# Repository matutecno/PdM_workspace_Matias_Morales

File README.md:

STM32 University Projects - Coursework Solutions
This repository contains solutions for the exercises proposed in my Embedded Systems courses.

⚠️ Important: Library Dependency
These projects rely on shared drivers stored in the Personal_libs folder. If a project does not compile, you must link this folder to your environment:

Right-click on the project -> Select "Properties".

Go to C/C++ General -> Paths and Symbols.

Select the "Source Location" tab.

Click on "Link Folder...".

Folder name: Enter Personal_libs.

Check the box "Link to folder in the file system".

Click "Browse..." and select your local Personal_libs directory.

Click OK -> Apply and Close.

📂 How to Add New Libraries to the Project
If you add a new module (like Delay or JSNSR04T) to the Personal_libs folder, follow these steps to ensure the IDE and the Compiler (GCC) recognize them:

1. Refresh the Project Explorer
After moving or creating files in your Linux file system (ThinkPad), the IDE needs to sync:

Right-click on the Personal_libs folder in the Project Explorer.

Select Refresh (or simply press F5). The new Inc and Src folders should now be visible.

2. Configure Include Paths (CRITICAL)
Even if the files are visible in the explorer, the compiler won't find the .h files unless you explicitly tell it where to look:

Right-click on the project name -> Properties.

Navigate to C/C++ Build -> Settings.

Under the Tool Settings tab, go to: MCU GCC Compiler -> Include paths.

Click the Add... icon (the page with the + symbol).

Click on Workspace..., navigate to the specific Inc folder (e.g., Personal_libs/Delay/Inc), and click OK.

Click Apply and Close.

Note: You must repeat step 2 for every new library module you create to avoid "No such file or directory" errors during compilation.

Project Directory

📂 Excercise 1
LED Blink: Basic implementation using External Interrupts (EXTI) to handle push-button inputs, avoiding CPU blocking.

📂 Excercise 2
Non-blocking Delays: Timing implementation using the HAL_GetTick() method to allow multitasking.

Bonus Exercise: Found in the folder ending in _3.

Custom Driver: I developed a modular library (del.c and del.h) to encapsulate delay logic for future projects.

Theory: Check Notes.txt within the project folder for the technical Q&A.

📂 Exercise 3
No comments

📂 Exercise 4
Finite machine states

📂 Exercise 5

Part 1: Polling UART Driver

**Platform:** Nucleo-F446RE (STM32F446RE, 84 MHz)
**IDE:** STM32CubeIDE
**Course:** Microcontroller Programming — FIUBA

## Description

Implementation of a UART driver over USART2 in polling mode, without DMA or interrupts. The driver encapsulates the HAL handle and exposes a high-level API for sending and receiving strings.

## Serial Port Configuration

| Parameter       | Value     |
|-----------------|-----------|
| Instance        | USART2    |
| Baud rate       | 9600      |
| Data bits       | 8         |
| Parity          | Odd       |
| Stop bits       | 1         |
| Flow control    | None      |
| Oversampling    | x16       |
| Pins            | PA2 (TX), PA3 (RX) |

> The serial terminal must be configured as **9600 8-Odd-1**.

## Driver Files

| File | Description |
|------|-------------|
| `STM32CubeIDE/Drivers/API_uart.c/Src/API_uart.c` | Driver implementation |
| `STM32CubeIDE/Drivers/API_uart.c/Inc/API_uart.h` | Public interface |

## API

```c
bool uartInit(void);
void uartSendString(uint8_t *pstring);
void uartSendStringSize(uint8_t *pstring, uint16_t size);
void uartReceiveStringSize(uint8_t *pstring, uint16_t size);
```

- `uartInit`: initializes USART2 and prints the port configuration to the console. Returns `1` on success, `0` on error.
- `uartSendString`: transmits a null-terminated string.
- `uartSendStringSize`: transmits exactly `size` bytes, one byte at a time.
- `uartReceiveStringSize`: receives bytes until `\n` or until `size` bytes are read. Blocks until reception is complete.

## Main Behavior

On startup, `uartInit` prints the port configuration. The main loop then:
1. Sends `buffer` over UART
2. Waits 500 ms
3. Sends `buffer2` over UART
4. Waits 500 ms
5. Sends `buffer3` over UART and waits to receive a string from the terminal
6. The received string is stored in `buffer3` for the next cycle

## Clock

- Source: HSE 8 MHz
- PLL: PLLM=8, PLLN=336, PLLP=DIV4 → SYSCLK = 84 MHz
- APB1 = 42 MHz (USART2 clock source)
- Voltage scaling: SCALE2

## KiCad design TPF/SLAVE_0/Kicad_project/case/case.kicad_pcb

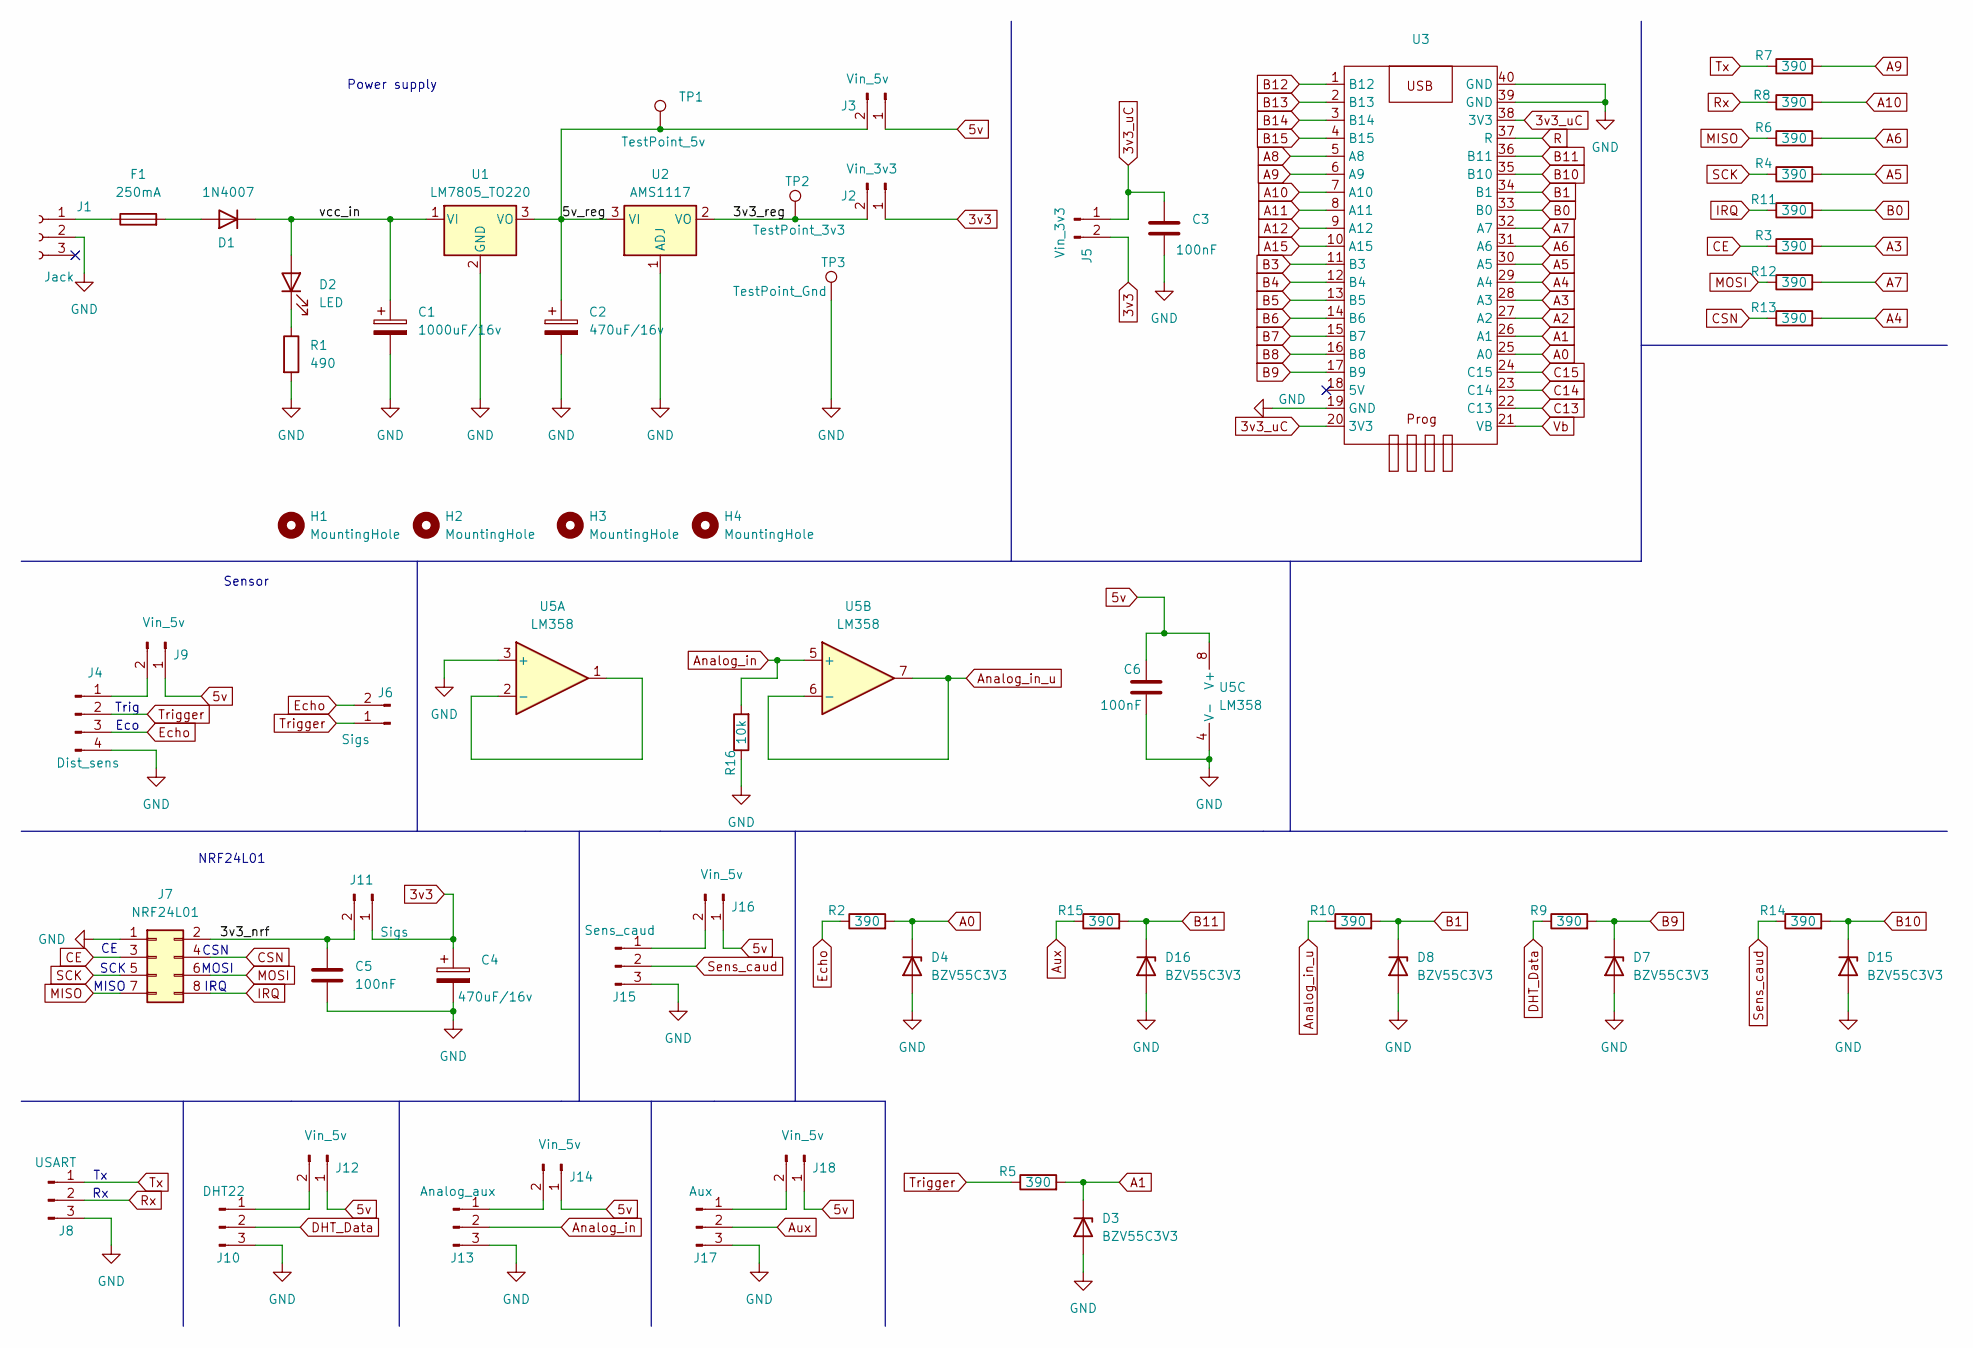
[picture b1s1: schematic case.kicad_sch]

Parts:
C1: 1000uF/16v; CP_Radial_D10.0mm_P5.00mm
C2, C4: 470uF/16v; CP_Radial_D8.0mm_P3.50mm
C3, C5, C6: 100nF; C_1206_3216Metric
D1: 1N4007; D_SMA_Handsoldering
D2: LED; LED_D3.0mm
D3, D4, D7, D8, D15, D16: BZV55C3V3; D_MiniMELF
F1: 250mA; Fuse_Littelfuse_395Series
H1, H2, H3, H4: MountingHole; MountingHole_3mm
J1: Jack; BarrelJack_Horizontal
J2, J5: Vin_3v3; PinHeader_1x02_P2.54mm_Vertical
J3, J9, J12, J14, J16, J18: Vin_5v; PinHeader_1x02_P2.54mm_Vertical
J4: Dist_sens; JST_PH_B4B-PH-K_1x04_P2.00mm_Vertical
J6, J11: Sigs; PinHeader_1x02_P2.54mm_Vertical
J7: NRF24L01
J8: USART; JST_XA_B03B-XASK-1_1x03_P2.50mm_Vertical
J10: DHT22; JST_XA_B03B-XASK-1_1x03_P2.50mm_Vertical
J13: Analog_aux; JST_XA_B03B-XASK-1_1x03_P2.50mm_Vertical
J15: Sens_caud; JST_XA_B03B-XASK-1_1x03_P2.50mm_Vertical
J17: Aux; JST_XA_B03B-XASK-1_1x03_P2.50mm_Vertical
R1: 490; R_1206_3216Metric
R2, R3, R4, R5, R6, R7, R8, R9, R10, R11, R12, R13, R14, R15: 390; R_1206_3216Metric
R16: 10k; R_1206_3216Metric
TP1: TestPoint_5v; TestPoint_Pad_D2.0mm
TP2: TestPoint_3v3; TestPoint_Pad_D2.0mm
TP3: TestPoint_Gnd; TestPoint_Pad_D2.0mm
U1: LM7805_TO220; TO-220-3_Vertical
U2: AMS1117; SOT-223-3_TabPin2
U3: Bluepill
U5: LM358; SOIC-8_3.9x4.9mm_P1.27mm

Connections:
3v3: C4.1, J2.1, J5.2, J11.1
3v3_uC: C3.1, J5.1, U3.20 (3V3), U3.38 (3V3)
5v: C6.1, J3.1, J9.1, J12.1, J14.1, J16.1, J18.1, U5.8 (V+)
/3v3_nrf: C5.1, J7.2, J11.2
/3v3_reg: J2.2, TP2.1, U2.2 (VO)
/5v_reg: C2.1, J3.2, TP1.1, U1.3 (VO), U2.3 (VI)
/vcc_in: C1.1, D1.1 (K), D2.2 (A), U1.1 (VI)
A0: D4.1 (K), R2.2, U3.25 (A0)
A1: D3.1 (K), R5.2, U3.26 (A1)
A2: U3.27 (A2)
A3: R3.2, U3.28 (A3)
A4: R13.2, U3.29 (A4)
A5: R4.2, U3.30 (A5)
A6: R6.2, U3.31 (A6)
A7: R12.2, U3.32 (A7)
A8: U3.5 (A8)
A9: R7.2, U3.6 (A9)
A10: R8.2, U3.7 (A10)
A11: U3.8 (A11)
A12: U3.9 (A12)
A15: U3.10 (A15)
Analog_in: J13.2, R16.2, U5.5 (+)
Analog_in_u: R10.1, U5.6 (-), U5.7
Aux: J17.2, R15.1
B0: R11.2, U3.33 (B0)
B1: D8.1 (K), R10.2, U3.34 (B1)
B3: U3.11 (B3)
B4: U3.12 (B4)
B5: U3.13 (B5)
B6: U3.14 (B6)
B7: U3.15 (B7)
B8: U3.16 (B8)
B9: D7.1 (K), R9.2, U3.17 (B9)
B10: D15.1 (K), R14.2, U3.35 (B10)
B11: D16.1 (K), R15.2, U3.36 (B11)
B12: U3.1 (B12)
B13: U3.2 (B13)
B14: U3.3 (B14)
B15: U3.4 (B15)
C13: U3.22 (C13)
C14: U3.23 (C14)
C15: U3.24 (C15)
CE: J7.3, R3.1
CSN: J7.4, R13.1
DHT_Data: J10.2, R9.1
Echo: J4.3, J6.2, R2.1
GND: C1.2, C2.2, C3.2, C4.2, C5.2, C6.2, D3.2 (A), D4.2 (A), D7.2 (A), D8.2 (A), D15.2 (A), D16.2 (A), J1.2, J4.4, J7.1, J8.3, J10.3, J13.3, J15.3, J17.3, R1.2, R16.1, TP3.1, U1.2 (GND), U2.1 (ADJ), U3.19 (GND), U3.39 (GND), U3.40 (GND), U5.3 (+), U5.4 (V-)
IRQ: J7.8, R11.1
MISO: J7.7, R6.1
MOSI: J7.6, R12.1
unnamed: D1.2 (A), F1.2
unnamed: D2.1 (K), R1.1
unnamed: F1.1, J1.1
unnamed: J4.1, J9.2
unnamed: J10.1, J12.2
unnamed: J13.1, J14.2
unnamed: J15.1, J16.2
unnamed: J17.1, J18.2
unnamed: U5.1, U5.2 (-)
R: U3.37 (R)
Rx: J8.2, R8.1
SCK: J7.5, R4.1
Sens_caud: J15.2, R14.1
Trigger: J4.2, J6.1, R5.1
Tx: J8.1, R7.1
Vb: U3.21 (VB)

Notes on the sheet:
IRQ
Trig
MOSI
Sensor
MISO
CSN
SCK
Power supply
Eco
NRF24L01

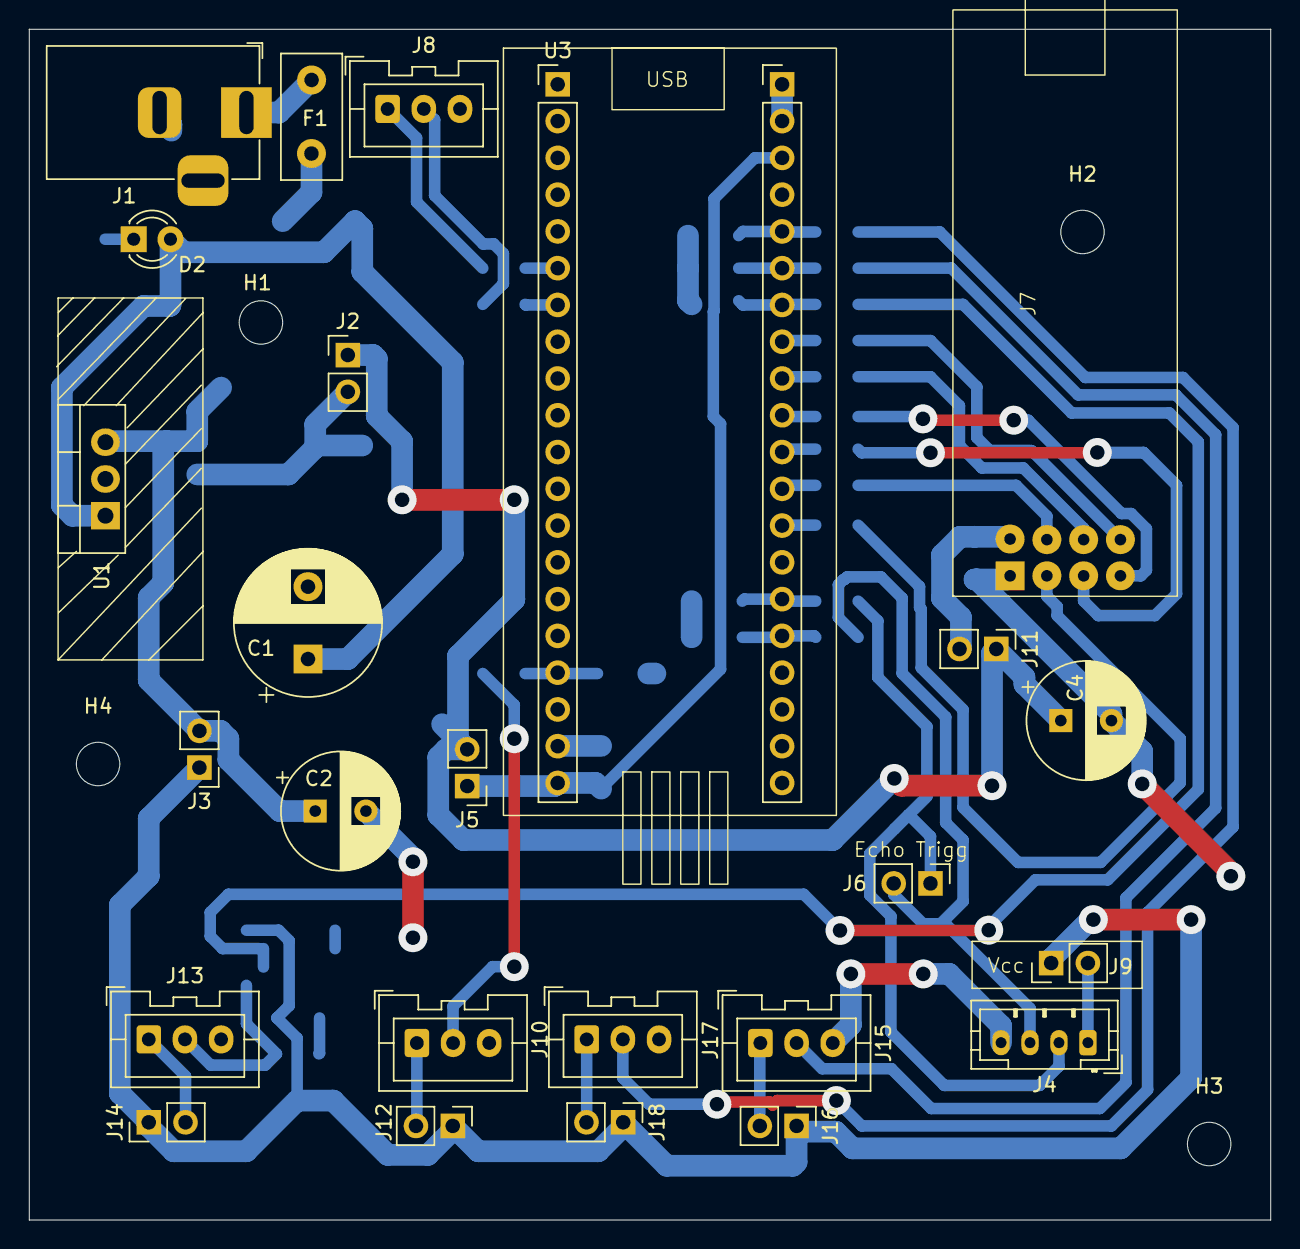
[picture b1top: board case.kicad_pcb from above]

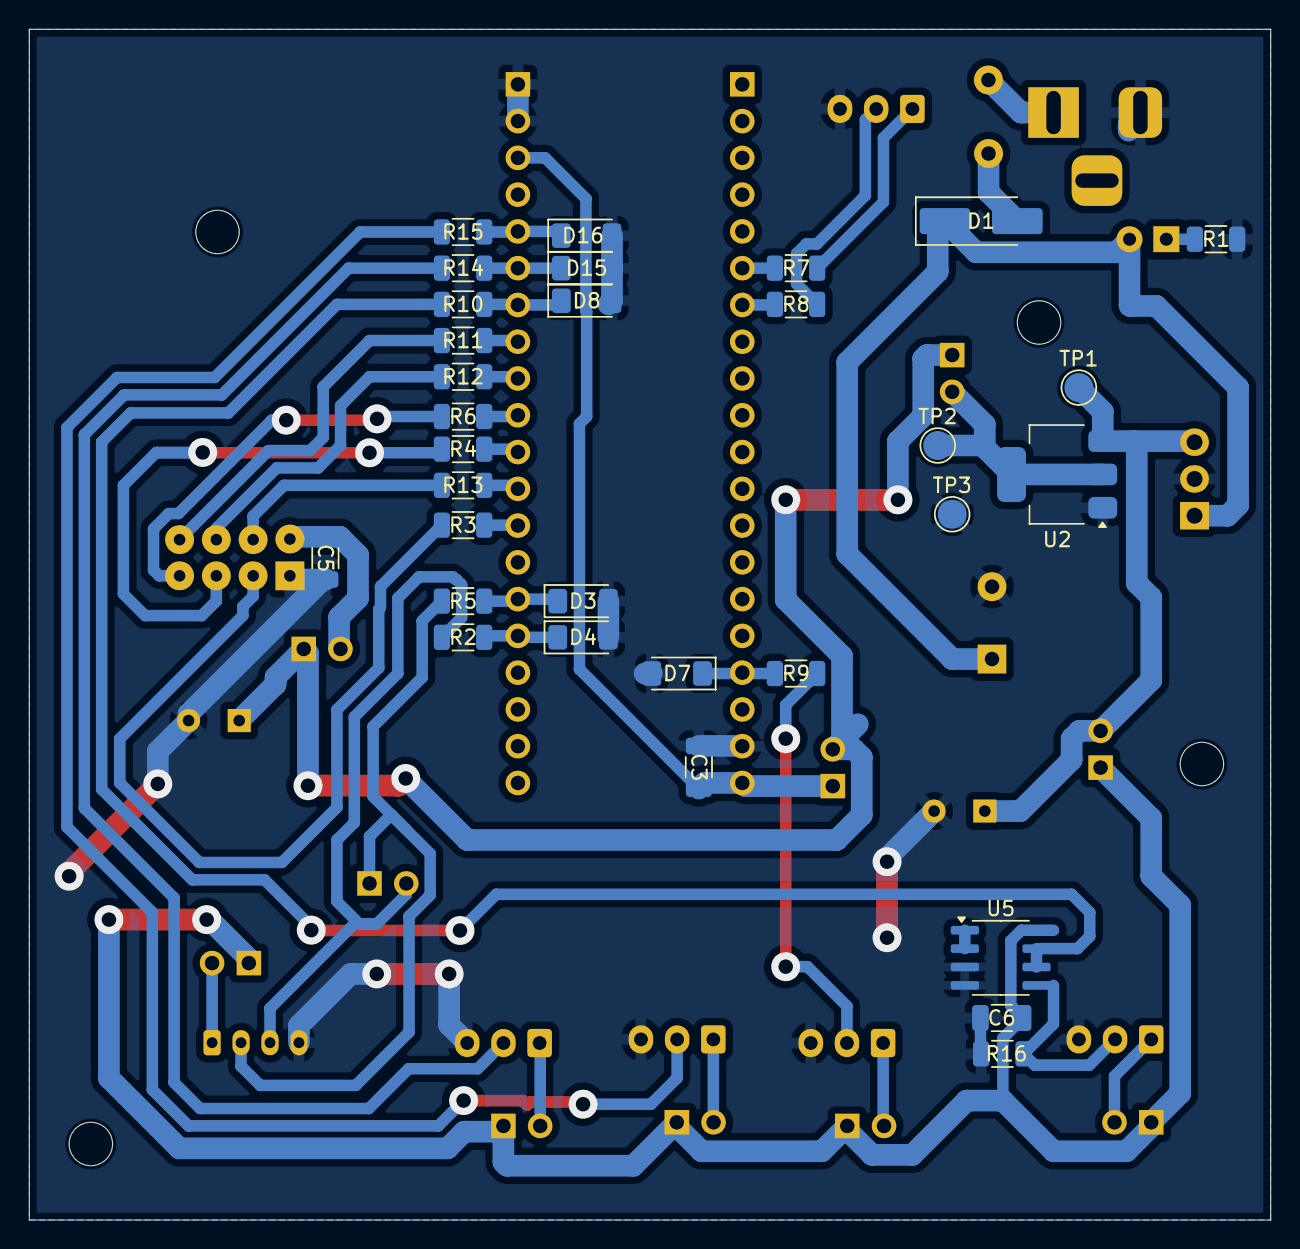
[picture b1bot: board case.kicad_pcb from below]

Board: 2 copper layers, 85.8 x 82.2 mm, 60 parts (31 on the bottom side), 46 nets.

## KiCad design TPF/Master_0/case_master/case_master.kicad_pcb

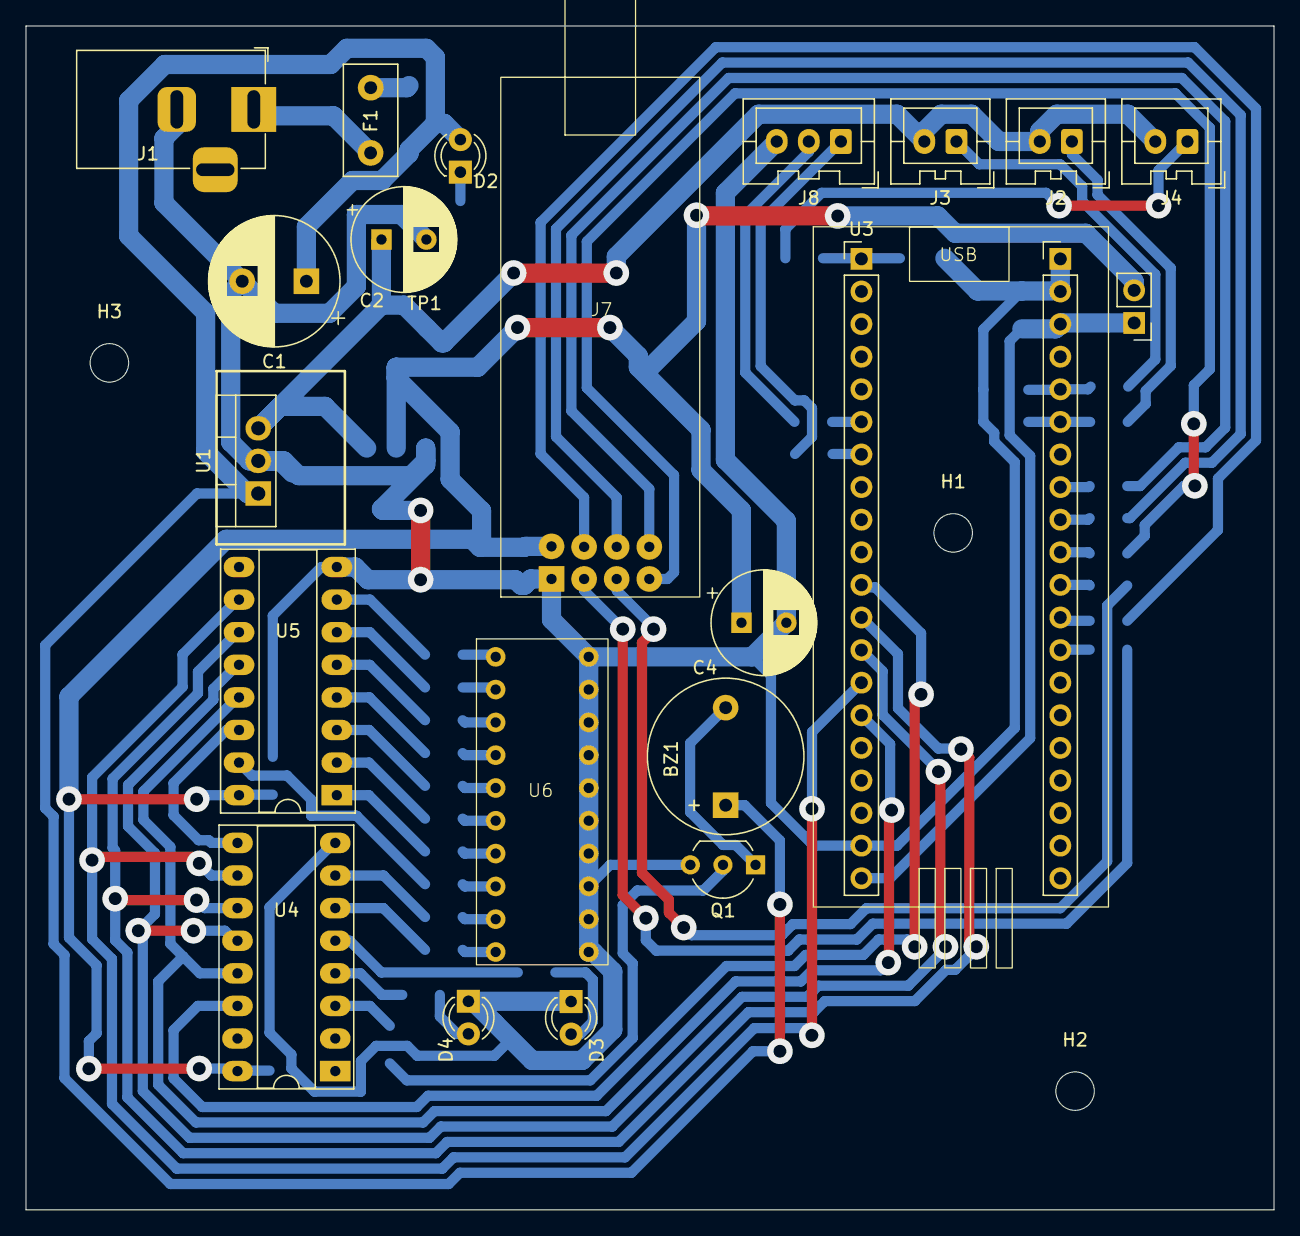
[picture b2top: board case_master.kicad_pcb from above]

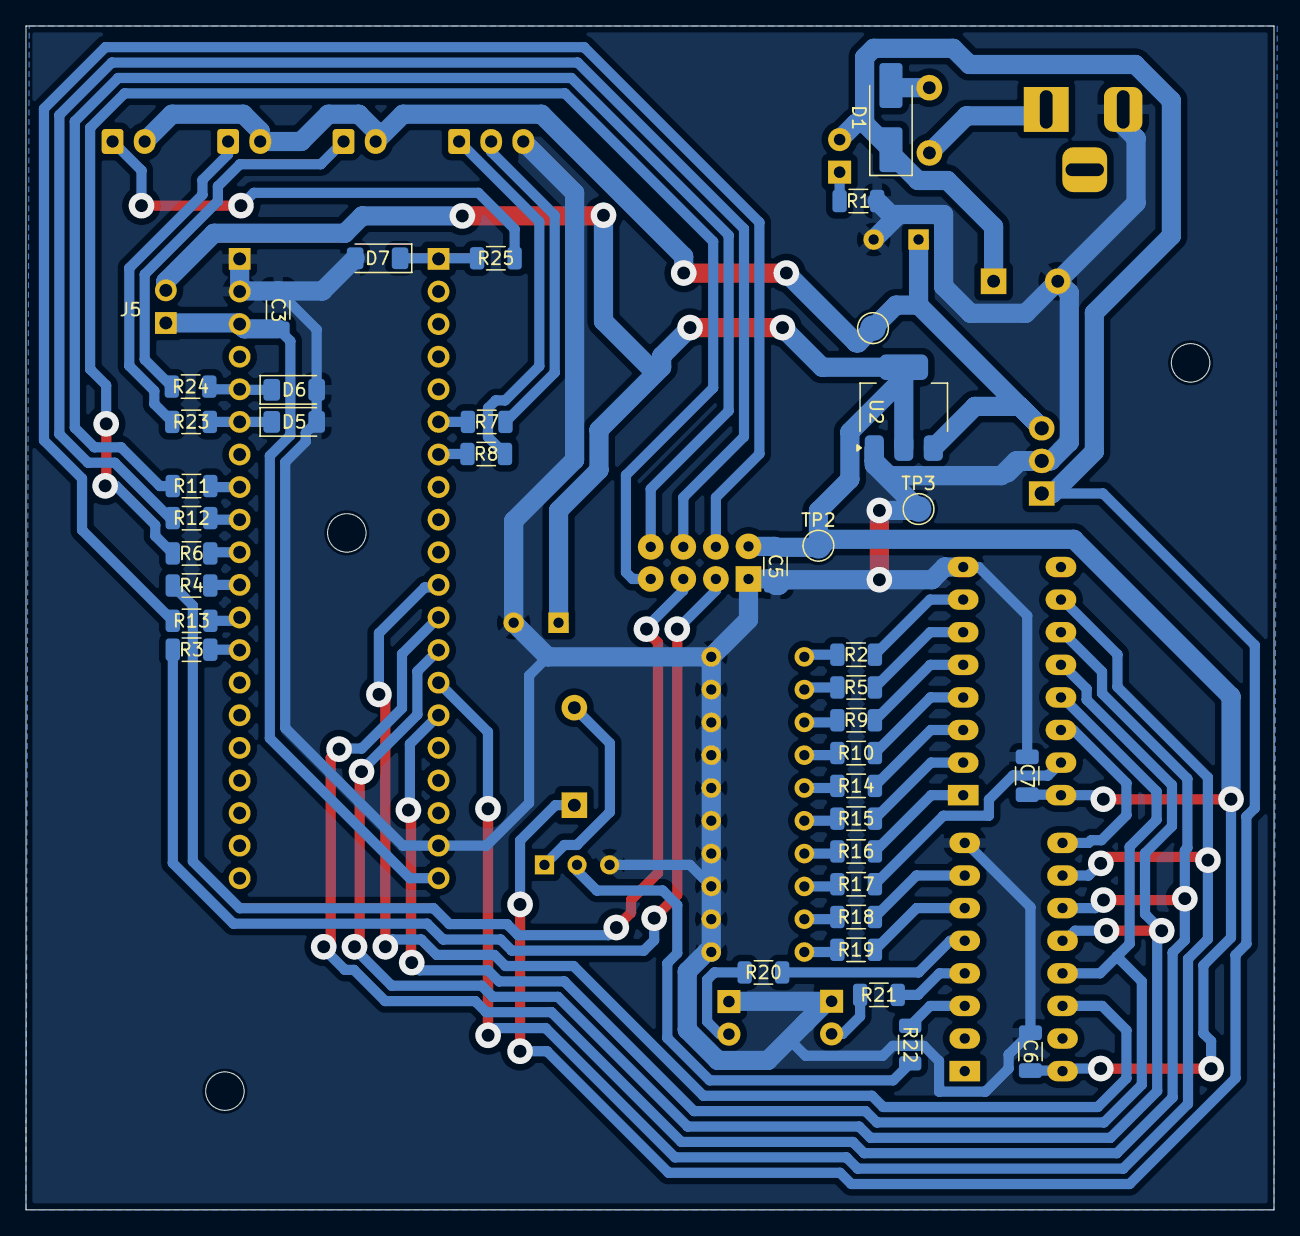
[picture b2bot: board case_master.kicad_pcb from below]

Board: 2 copper layers, 97.2 x 92.2 mm, 61 parts (37 on the bottom side), 63 nets.

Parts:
BZ1: Buzzer; Buzzer_12x9.5RM7.6
C1: 1000uF/16v; CP_Radial_D10.0mm_P5.00mm
C2, C4: 470uF/16v; CP_Radial_D8.0mm_P3.50mm
C3, C5, C6, C7: 100nF; C_1206_3216Metric
D1: 1N4007; D_SMA_Handsoldering
D2, D3, D4: LED; LED_D3.0mm
D5, D6, D7: BZV55C3V3; D_MiniMELF
F1: 250mA; Fuse_Littelfuse_395Series
H1, H2, H3: MountingHole; MountingHole_3mm
J1: Jack; BarrelJack_Horizontal
J2, J3, J4: Pul_0; JST_XA_B02B-XASK-1_1x02_P2.50mm_Vertical
J5: Vin_3v3; PinHeader_1x02_P2.54mm_Vertical
J7: NRF24L01
J8: USART; JST_XA_B03B-XASK-1_1x03_P2.50mm_Vertical
Q1: BC337; TO-92_Inline_Wide
R1: 490; R_1206_3216Metric
R2, R5, R9, R10, R14, R15, R16, R17, R18, R19, R20, R21: 270; R_1206_3216Metric
R3, R4, R6, R7, R8, R11, R12, R13: 390; R_1206_3216Metric
R22: 4k7; R_1206_3216Metric
R23, R24, R25: 1k; R_1206_3216Metric
TP1: TestPoint_5v; TestPoint_Pad_D2.0mm
TP2: TestPoint_3v3; TestPoint_Pad_D2.0mm
TP3: TestPoint_Gnd; TestPoint_Pad_D2.0mm
U1: LM7805_TO220; TO-220-3_Vertical
U2: AMS1117; SOT-223-3_TabPin2
U3: Bluepill
U4, U5: 74HC595; DIP-16_W7.62mm_Socket_LongPads
U6: Dis_1; Led_Bar

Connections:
3v3: C4.1, C5.1, C6.1, C7.1, J5.2, J7.2, TP2.1, U2.2 (VO), U4.16 (VCC), U5.16 (VCC)
3v3_uC: C3.1, J5.1, U3.20 (3V3), U3.38 (3V3)
5v: C2.1, J2.2, J3.2, J4.2, TP1.1, U1.3 (VO), U2.3 (VI)
12V: BZ1.1 (+), C1.1, D1.1 (K), D2.2 (A), U1.1 (VI)
Buzz: R22.1, U4.3 (QD)
CE: J7.3, R3.1
CE_u: R3.2, U3.28 (A3)
CSN: J7.4, R13.1
CSN_u: R13.2, U3.29 (A4)
GND: C1.2, C2.2, C3.2, C4.2, C5.2, C6.2, C7.2, D3.1 (K), D4.1 (K), D5.2 (A), D6.2 (A), D7.2 (A), J1.2, J7.1, J8.3, Q1.3 (E), R1.2, TP3.1, U1.2 (GND), U2.1 (ADJ), U3.19 (GND), U3.39 (GND), U3.40 (GND), U4.8 (GND), U5.8 (GND), U6.10 (GND), U6.11 (GND), U6.12 (GND), U6.13 (GND), U6.14 (GND), U6.15 (GND), U6.16 (GND), U6.17 (GND), U6.18 (GND), U6.19 (GND)
IRQ: J7.8, R11.1
IRQ_u: R11.2, U3.33 (B0)
L0: R19.1, U4.6 (QG)
L1: R18.1, U4.7 (QH)
L2: R17.1, U5.15 (QA)
L3: R16.1, U5.1 (QB)
L4: R15.1, U5.2 (QC)
L5: R14.1, U5.3 (QD)
L6: R10.1, U5.4 (QE)
L7: R9.1, U5.5 (QF)
L8: R5.1, U5.6 (QG)
L9: R2.1, U5.7 (QH)
Lev_Bat: R21.1, U4.4 (QE)
Lev_Wat: R20.1, U4.5 (QF)
MISO: J7.7, R6.1
MISO_u: R6.2, U3.31 (A6)
MOSI: J7.6, R12.1
MOSI_u: R12.2, U3.32 (A7)
unnamed: BZ1.2 (-), Q1.1 (C)
unnamed: D1.2 (A), F1.2
unnamed: D2.1 (K), R1.1
unnamed: D3.2 (A), R20.2
unnamed: D4.2 (A), R21.2
unnamed: F1.1, J1.1
unnamed: Q1.2 (B), R22.2
unnamed: U4.9 (QH'), U5.14 (SER)
unnamed: R19.2, U6.0
unnamed: R18.2, U6.1
unnamed: R17.2, U6.2
unnamed: R16.2, U6.3
unnamed: R15.2, U6.4
unnamed: R14.2, U6.5
unnamed: R10.2, U6.6
unnamed: R9.2, U6.7
unnamed: R5.2, U6.8
unnamed: R2.2, U6.9
OE: U3.15 (B7), U4.13 (~OE), U5.13 (~OE)
P0: J2.1, R23.1
P1: J3.1, R24.1
P2: J4.1, R25.1
Pul_0: D5.1 (K), R23.2, U3.35 (B10)
Pul_1: D6.1 (K), R24.2, U3.36 (B11)
Pul_2: D7.1 (K), R25.2, U3.1 (B12)
RCLK: U3.13 (B5), U4.12 (RCLK), U5.12 (RCLK)
Rx: J8.1, R8.1
Rx_u: R8.2, U3.7 (A10)
SCK: J7.5, R4.1
SCK_u: R4.2, U3.30 (A5)
SER: U3.11 (B3), U4.14 (SER)
SRCLK: U3.12 (B4), U4.11 (SRCLK), U5.11 (SRCLK)
SRCLR: U3.14 (B6), U4.10 (~SRCLR), U5.10 (~SRCLR)
Tx: J8.2, R7.1
Tx_u: R7.2, U3.6 (A9)

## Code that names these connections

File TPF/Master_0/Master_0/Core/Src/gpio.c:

/* USER CODE BEGIN Header */
/**
  ******************************************************************************
  * @file    gpio.c
  * @brief   This file provides code for the configuration
  *          of all used GPIO pins.
  ******************************************************************************
  * @attention
  *
  * Copyright (c) 2026 STMicroelectronics.
  * All rights reserved.
  *
  * This software is licensed under terms that can be found in the LICENSE file
  * in the root directory of this software component.
  * If no LICENSE file comes with this software, it is provided AS-IS.
  *
  ******************************************************************************
  */
/* USER CODE END Header */

/* Includes ------------------------------------------------------------------*/
#include "gpio.h"

/* USER CODE BEGIN 0 */

/* USER CODE END 0 */

/*----------------------------------------------------------------------------*/
/* Configure GPIO                                                             */
/*----------------------------------------------------------------------------*/
/* USER CODE BEGIN 1 */

/* USER CODE END 1 */

/** Configure pins as
        * Analog
        * Input
        * Output
        * EVENT_OUT
        * EXTI
*/
void MX_GPIO_Init(void)
{

  GPIO_InitTypeDef GPIO_InitStruct = {0};

  /* GPIO Ports Clock Enable */
  __HAL_RCC_GPIOC_CLK_ENABLE();
  __HAL_RCC_GPIOD_CLK_ENABLE();
  __HAL_RCC_GPIOA_CLK_ENABLE();
  __HAL_RCC_GPIOB_CLK_ENABLE();

  /*Configure GPIO pin Output Level */
  HAL_GPIO_WritePin(LED_GREEN_GPIO_Port, LED_GREEN_Pin, GPIO_PIN_RESET);

  /*Configure GPIO pin Output Level */
  HAL_GPIO_WritePin(NRF_CE_GPIO_Port, NRF_CE_Pin, GPIO_PIN_RESET);

  /*Configure GPIO pin Output Level */
  HAL_GPIO_WritePin(NRF_CSN_GPIO_Port, NRF_CSN_Pin, GPIO_PIN_SET);

  /*Configure GPIO pin Output Level */
  HAL_GPIO_WritePin(GPIOB, SER_Pin|SRCLK_Pin|RCLK_Pin|OE_Pin, GPIO_PIN_RESET);

  /*Configure GPIO pin Output Level */
  HAL_GPIO_WritePin(SRCLR_GPIO_Port, SRCLR_Pin, GPIO_PIN_SET);

  /*Configure GPIO pin : LED_GREEN_Pin */
  GPIO_InitStruct.Pin = LED_GREEN_Pin;
  GPIO_InitStruct.Mode = GPIO_MODE_OUTPUT_PP;
  GPIO_InitStruct.Pull = GPIO_NOPULL;
  GPIO_InitStruct.Speed = GPIO_SPEED_FREQ_LOW;
  HAL_GPIO_Init(LED_GREEN_GPIO_Port, &GPIO_InitStruct);

  /*Configure GPIO pins : NRF_CE_Pin NRF_CSN_Pin */
  GPIO_InitStruct.Pin = NRF_CE_Pin|NRF_CSN_Pin;
  GPIO_InitStruct.Mode = GPIO_MODE_OUTPUT_PP;
  GPIO_InitStruct.Pull = GPIO_NOPULL;
  GPIO_InitStruct.Speed = GPIO_SPEED_FREQ_LOW;
  HAL_GPIO_Init(GPIOA, &GPIO_InitStruct);

  /*Configure GPIO pins : NRF_IRQ_Pin Pul_0_Pin Pul_1_Pin Pul_2_Pin */
  GPIO_InitStruct.Pin = NRF_IRQ_Pin|Pul_0_Pin|Pul_1_Pin|Pul_2_Pin;
  GPIO_InitStruct.Mode = GPIO_MODE_IT_FALLING;
  GPIO_InitStruct.Pull = GPIO_PULLUP;
  HAL_GPIO_Init(GPIOB, &GPIO_InitStruct);

  /*Configure GPIO pins : SER_Pin SRCLK_Pin RCLK_Pin SRCLR_Pin
                           OE_Pin */
  GPIO_InitStruct.Pin = SER_Pin|SRCLK_Pin|RCLK_Pin|SRCLR_Pin
                          |OE_Pin;
  GPIO_InitStruct.Mode = GPIO_MODE_OUTPUT_PP;
  GPIO_InitStruct.Pull = GPIO_NOPULL;
  GPIO_InitStruct.Speed = GPIO_SPEED_FREQ_LOW;
  HAL_GPIO_Init(GPIOB, &GPIO_InitStruct);

  /* EXTI interrupt init*/
  HAL_NVIC_SetPriority(EXTI0_IRQn, 0, 0);
  HAL_NVIC_EnableIRQ(EXTI0_IRQn);

  HAL_NVIC_SetPriority(EXTI15_10_IRQn, 0, 0);
  HAL_NVIC_EnableIRQ(EXTI15_10_IRQn);

}

/* USER CODE BEGIN 2 */

/* USER CODE END 2 */

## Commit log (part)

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2026-03-08 Ejercicio 1 - B
2026-03-08 Add notes
2026-03-10 Ejercicio 1
2026-03-15 TP2, puntos 1 2 3
2026-03-15 Agrega comentario ej 2, pendiente versión mejorada
2026-03-15 Modifica delay y agrega funciones en biblioteca del.c para usos futuros
2026-03-16 Add README.md
2026-03-16 Modifica README.md
2026-03-20 Move library to Driver folder
2026-03-24 Modify ej2a, add personal libs
2026-03-24 Actualiza TP3
2026-03-24 Modify readme.md
2026-03-27 Testcase pulsador ej4
2026-03-30 Actualiza varios
2026-03-30 Agrega TP4
2026-04-03 Agrega TP5, parte 1
2026-04-05 Agrega EJ2
2026-04-13 Agrega propuesta tpf
2026-04-18 Add tpf
2026-04-19 Update gral
2026-04-26 Add ports.h
